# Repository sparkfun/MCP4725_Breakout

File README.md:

MCP4725_Breakout
================
[  
*Breakout Board for MCP4725 I2C DAC (BOB-12918)*](https://www.sparkfun.com/products/12918)

The MCP4725 is an I<sup>2</sup>C controlled Digital-to-Analog converter (DAC). It allows you to send an analog signal from a digital source.

Repository Contents
-------------------
* **/Hardware** - Eagle PCB layout files
* **/Production** - Test bed files and production panel files

Version History
---------------
* [BOB-08736](https://www.sparkfun.com/products/8736) -Version 1.3. Now retired. 

License Information
-------------------
The hardware is released under [Creative Commons ShareAlike 4.0 International](https://creativecommons.org/licenses/by-sa/4.0/).
The code is beerware; if you see me (or any other SparkFun employee) at the local, and you've found our code helpful, please buy us a round!

Distributed as-is; no warranty is given.

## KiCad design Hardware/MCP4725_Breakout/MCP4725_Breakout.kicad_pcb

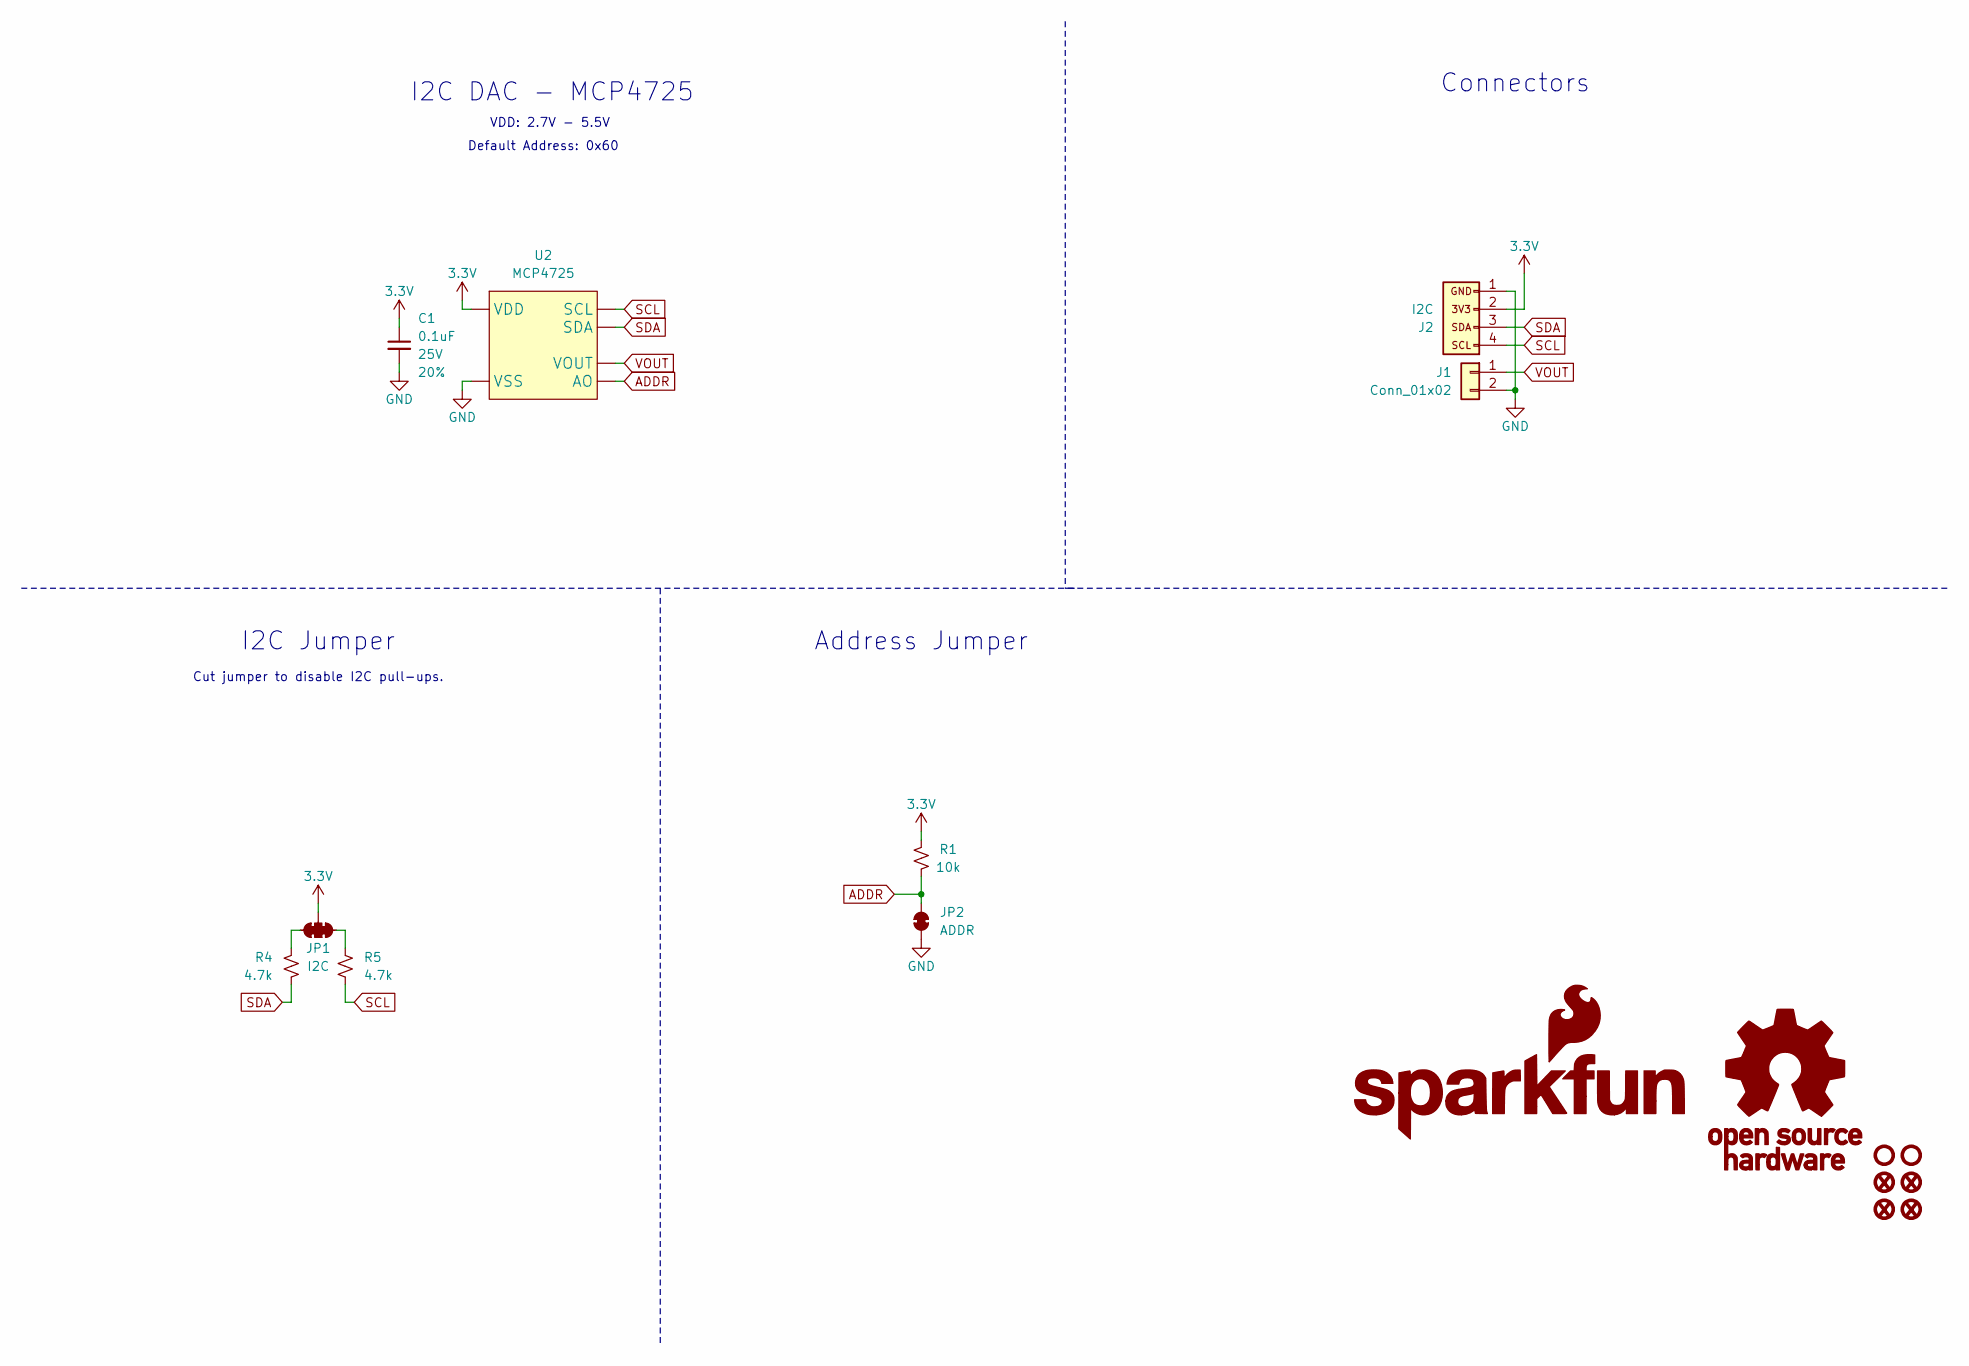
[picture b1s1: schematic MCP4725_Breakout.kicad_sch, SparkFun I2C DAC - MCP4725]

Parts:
C1: 0.1uF; C_0603_1608Metric; Voltage 25V; Tolerance 20%
FID1, FID2, FID3, FID4: Fiducial_0.5mm; Fiducial_0.5mm_Mask1mm
G1: OSHW_Logo; Creative_Commons_License
G2: SparkFun_Logo
J1: Conn_01x02; 1x02_P2.54mm
J2: I2C; 1x04_P2.54mm
JP1: I2C; Jumper_3_NC-2_Trace
JP2: ADDR; Jumper_2_NC_Trace
R1: 10k; R_0603_1608Metric
R4, R5: 4.7k; R_0603_1608Metric
ST1, ST2: Standoff
U2: MCP4725; SOT23-6

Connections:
3.3V: C1.1, J2.2, JP1.2 (B), R1.2, U2.3 (VDD)
ADDR: JP2.2 (B), R1.1, U2.6 (AO)
GND: C1.2, J1.2, J2.1, JP2.1 (A), U2.2 (VSS)
unnamed: JP1.1 (A), R5.2
unnamed: JP1.3 (C), R4.2
SCL: J2.4, R5.1, U2.5 (SCL)
SDA: J2.3, R4.1, U2.4 (SDA)
VOUT: J1.1, U2.1 (VOUT)

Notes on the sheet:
Default Address: 0x60
VDD: 2.7V - 5.5V
I2C DAC - MCP4725
Cut jumper to disable I2C pull-ups.
Address Jumper
I2C Jumper
Connectors

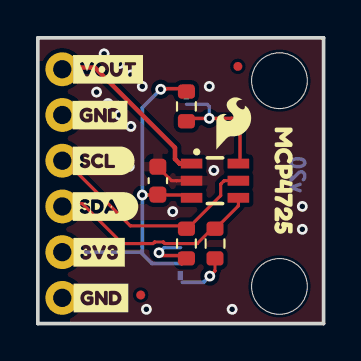
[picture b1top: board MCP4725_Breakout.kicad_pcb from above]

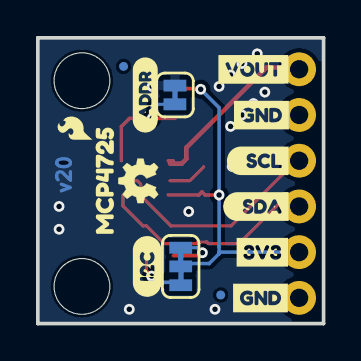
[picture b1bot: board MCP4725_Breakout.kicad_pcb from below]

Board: 2 copper layers, 15.9 x 15.9 mm, 33 parts (14 on the bottom side), 8 nets.

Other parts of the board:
Ref**: Val**; OSHW_Logo_2.5mm
kibuzzard-69B46D81, kibuzzard-69B46D81#2: G***; kibuzzard-69B46D81
kibuzzard-69B46D94, kibuzzard-69B46D94#2, kibuzzard-69B46D94#3, kibuzzard-69B46D94#4: G***; kibuzzard-69B46D94
kibuzzard-69B46DE0, kibuzzard-69B46DE0#2: G***; kibuzzard-69B46DE0
kibuzzard-69B46E1A, kibuzzard-69B46E1A#2: G***; kibuzzard-69B46E1A
kibuzzard-69B46E2A: G***; kibuzzard-69B46E2A
kibuzzard-69B46E2F: G***; kibuzzard-69B46E2F
kibuzzard-69B46E88: G***; kibuzzard-69B46E88
kibuzzard-69B46EE5: G***; kibuzzard-69B46EE5
kibuzzard-69B46EEC: G***; kibuzzard-69B46EEC
kibuzzard-69B976CB: G***; kibuzzard-69B976CB

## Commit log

2014-05-06 Lots of changes from v13 to v14
    Committing v_14 changes:
    *Corrected the IC footprint, both the original and Kade's update were
    both incorrect. The pin 1 indicator is now in the correct position.
    *New frame, updated logos, added OSHW logo
    *Switched up pinout for "standard" I2C pinout
    *Added jumper for I2C Address selection
2014-05-21 Addressed issues from first review
    added new jumper packages
    moved and rerouted to avoid cutting of silk text
    added extra GND pad for VOUT
2014-05-29 Final commit before protos
    Changed 10k pull-ups to 4.7k
    Added 10k to prevent shorts on I2C address selection
    Added hex values for address
    added name to symbol layer
    clean up and organize folders
2014-05-29 delete extra .brd file
    delete extra .brd file
2014-07-24 Fixed Silk, OUT and GND were swapped
    Fixed Silk, OUT and GND were swapped
2014-07-29 Last Commit before Reds
    Added my name to brd. file
    added Vcc levels to sch.
    changed file name so version # isn't there
    minor silk fixes due to vias.
2014-07-30 removed micro fiducial, added regulars
2014-07-30 changed location of fiducial
2014-07-31 created panel v14
2014-09-11 Updating README to new product links
2015-02-04 Corrected to generic SOT-23 library
    See engineering file audit, package issues for more information.
2026-03-11 Imports board files to KiCad
2026-03-13 Saves progress
2026-03-17 Adjusts the jumpers on the underside
2026-03-17 Saves progress before shifting board placement around screw terminals
2026-03-17 Moves the entire board such that the stand offs and plated through holes
    ...are evenly spaced relative to the edge. The standoffs and plated
    through holes did not move relative to each other.
2026-03-17 Copies design for Qwiic board
2026-03-17 Routes Qwiic Board, adds
2026-03-17 Adds measures, adds silk
2026-03-18 Fixes DAC symbol, aligns Qwiic connector, removes extra pour
2026-03-18 Fixes swapped pins on SCL/SDA
2026-03-18 Adds new gitignore
2026-03-19 Adds Qwiic Logo, power LED, adds "DAC" to product silk
    * Fixes the address jumper
2026-03-19 Changes dual to single jumper
2026-03-19 Fixes jumpers on more time
2026-03-26 Puts PTH on one side
2026-03-26 Adds measures, grows small board by another 1/8 inch in X/Y direction
2026-03-30 Adds gerbers
2026-04-02 Fixes trace widths
2026-04-06 Adds BOM and gerbers for small form factor version
2026-05-26 Removes 1x1 board

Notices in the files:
parts and their libraries:
Released under the Creative Commons Attribution Share-Alike 4.0 License
